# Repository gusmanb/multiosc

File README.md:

# MultiOsc
----
## Description
Two-channel 7Khz to 200Mhz clock/oscillator.

----
## Overview
MultiOsc is a very cheap two-channel clock generator which can be configured to generate frequencies from 8Khz to 200Mhz (180 to 200, depends on the SI5153 version) for less than 10€.

The device is based on the SI5351 clock generator, more concretely using the module sold in AliExpress (for less than 4€) which is very convenient as it already contains all the required external components to get it working immediately.

The device uses a STM32F103 module to control the clock generator and drive a 0.66" I2C screen.

## Schematic

The schematic is extremely simple, the three modules are connected through the I2C bus and five push buttons are used to control de menus, nothing more nothing else :)

## PCB

I also have included a very basic PCB to construct the device but it's not needed at all. I have assembled it using a protoboard and it works really well, but for anyone who wants to make it more robust the PCB is a good option.

Both, schematic and PCB are included under the "PCB" folder, it's a KiCad 6.0 project and it includes all the custom footprints for the modules in case you want to reuse them.

## BOM

The bill of materials is very reduced:

* STM32F103 module:  https://es.aliexpress.com/item/1005002441720435.html
* 0.66" OLED screen: https://es.aliexpress.com/item/1005002760899272.html
* SI5351 module:     https://es.aliexpress.com/item/32915414654.html
* Push buttons (5):  https://es.aliexpress.com/item/1005004001434474.html

I am 99.99999% sure the STM module uses a clone uC, not an original STM device, but as far as I can tell the device works flawlessly.

## STM32F103 bootloader

I have seen a lot of people complaining about the F103 modules failing to run the bootloader, but this is all a missunderstanding on how the bootloader works for the F103.

If you check carefully the [AN2606](https://www.st.com/resource/en/application_note/cd00167594-stm32-microcontroller-system-memory-boot-mode-stmicroelectronics.pdf) it clarifies the problem and is really simple, the STM32F10XXX family only has UART bootloader and the modules connect the USB connector to the USB pins from these devices, there is no integrated serial-to-usb converter so the bootloader will not work connecting only the USB port, you also need a serial-to-usb converter and connect it to pins PA9 and PA10, with this the device will be accessible from STM32CubeProgrammer.

In any case I recommend to use a ST-LINK/V2 or similar (I have an original one and a clone, both work but the original one is less prone to cause errors and can be upgraded, so if you can, buy an original one), it works a lot faster and allows to debug the code in real time.

## Firmware

The firmware project is a STM32CubeIde project, currently I have used the 1.9.0 version and it uses the standard drivers and two heavily modified libraries.

The first library is the SSD1306 library by afiskon and you can find the original here: https://github.com/afiskon/stm32-ssd1306
The second library is the SI5351 library by MR-DOS and you can find the original here: https://github.com/MR-DOS/Si5351-lib

As you can imagine the firmware itself is very simple, it creates a menu where you can change the two output frequencies and that's all, nothing else is needed, and as it relies on the two aforementioned libraries controlling the screen and the SI module is a breeze.

Beware that I found there is a problem with CubeMX, if you open the CubeMX file to reconfigure the HAL drivers, pinout or whatever the CubeMX does break the I2C configuration, for the F103 device it does not allow to configure the port speed and without the configuration the I2C bus does not work. If you need to reconfigure the hardware, after re-generating the files you will need to modify the file "stm32f1xx_hal_msp.c" and add to the I2C initialization, before the "HAL_GPIO_Init" call, this: 

	GPIO_InitStruct.Speed = GPIO_SPEED_FREQ_HIGH;

---

Have fun!

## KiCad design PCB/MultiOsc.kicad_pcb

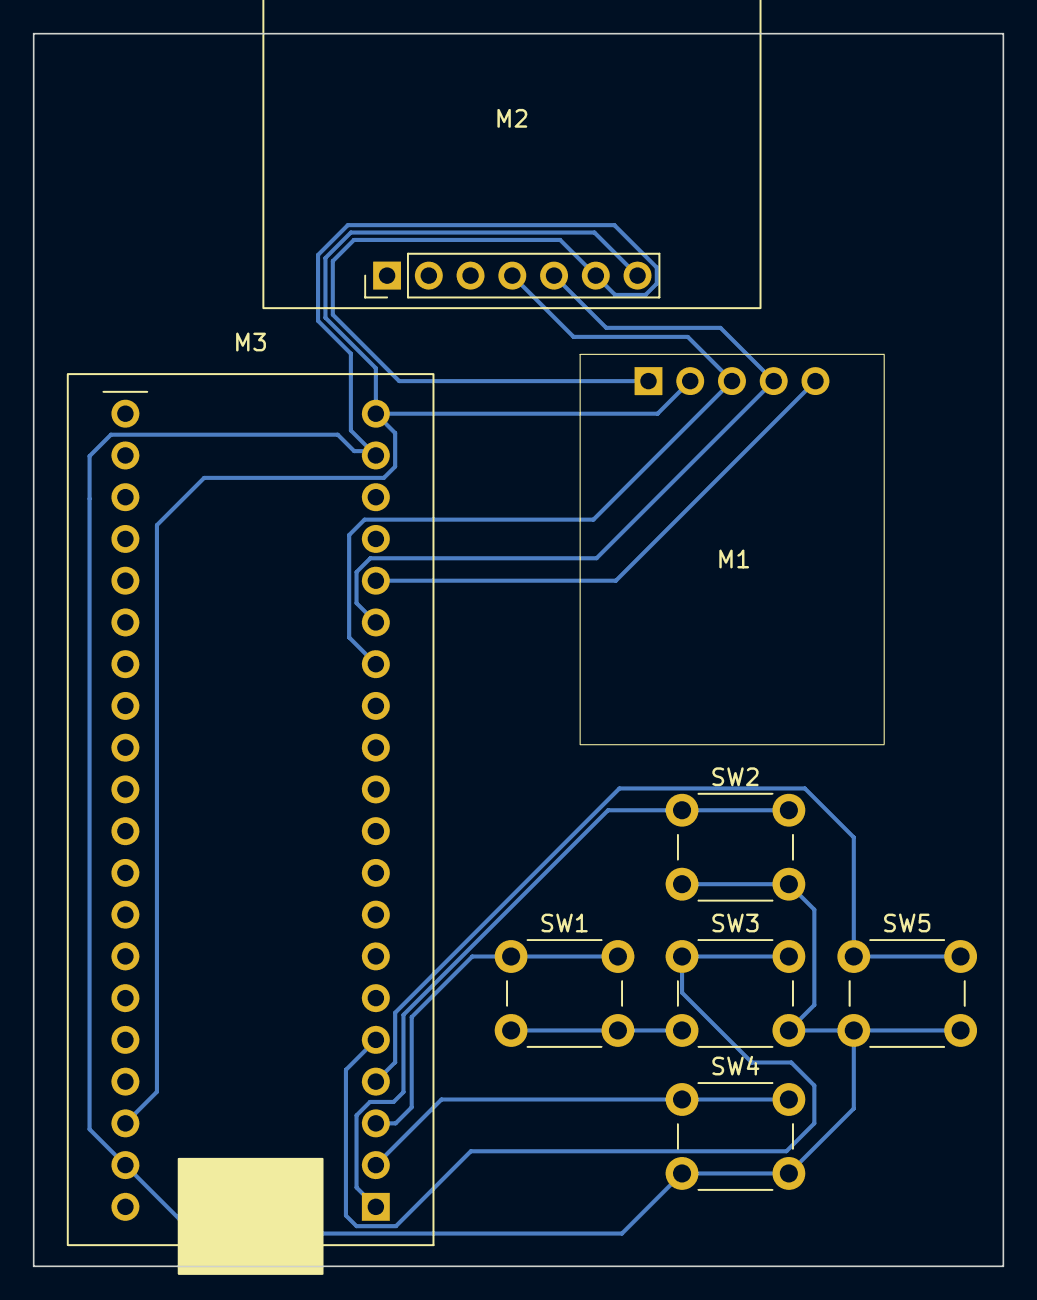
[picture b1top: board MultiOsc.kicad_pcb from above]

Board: 2 copper layers, 59.0 x 75.0 mm, 8 parts (0 on the bottom side), 10 nets.

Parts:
M1: OLED_066_Module
M2: SI5351_Module
M3: STM32F103_Module
SW1, SW2, SW3, SW4, SW5: SW_Push; SW_PUSH_6mm_H7.3mm

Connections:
/BTN_DOWN: M3.2 (B13), SW4.1
/BTN_ENTER: M3.5 (A8), SW3.1
/BTN_LEFT: M3.3 (B14), SW1.1
/BTN_RIGHT: M3.4 (B15), SW5.1
/BTN_UP: M3.1 (B12), SW2.1
/I2C_SCL: M1.3 (SCL), M2.4 (SCL), M3.14 (B6)
/I2C_SDA: M1.4 (SDA), M2.5 (SDA), M3.15 (B7)
/OLED_RES: M1.5 (RST), M3.16 (B8)
GND: M1.1 (GND), M2.6 (GND), M3.19 (G), M3.39 (G), SW1.2, SW2.2, SW3.2, SW4.2, SW5.2
VCC: M1.2 (VDD), M2.7 (VIN), M3.20 (3.3), M3.38 (3.3)

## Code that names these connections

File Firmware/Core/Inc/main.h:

/* USER CODE BEGIN Header */
/**
  ******************************************************************************
  * @file           : main.h
  * @brief          : Header for main.c file.
  *                   This file contains the common defines of the application.
  ******************************************************************************
  * @attention
  *
  * Copyright (c) 2022 STMicroelectronics.
  * All rights reserved.
  *
  * This software is licensed under terms that can be found in the LICENSE file
  * in the root directory of this software component.
  * If no LICENSE file comes with this software, it is provided AS-IS.
  *
  ******************************************************************************
  */
/* USER CODE END Header */

/* Define to prevent recursive inclusion -------------------------------------*/
#ifndef __MAIN_H
#define __MAIN_H

#ifdef __cplusplus
extern "C" {
#endif

/* Includes ------------------------------------------------------------------*/
#include "stm32f1xx_hal.h"

/* Private includes ----------------------------------------------------------*/
/* USER CODE BEGIN Includes */
#include "si5351.h"
#include "ssd1306.h"
/* USER CODE END Includes */

/* Exported types ------------------------------------------------------------*/
/* USER CODE BEGIN ET */

/* USER CODE END ET */

/* Exported constants --------------------------------------------------------*/
/* USER CODE BEGIN EC */

/* USER CODE END EC */

/* Exported macro ------------------------------------------------------------*/
/* USER CODE BEGIN EM */

/* USER CODE END EM */

/* Exported functions prototypes ---------------------------------------------*/
void Error_Handler(void);

/* USER CODE BEGIN EFP */

/* USER CODE END EFP */

/* Private defines -----------------------------------------------------------*/
#define LED_Pin GPIO_PIN_13
#define LED_GPIO_Port GPIOC
#define BTN_UP_Pin GPIO_PIN_12
#define BTN_UP_GPIO_Port GPIOB
#define BTN_DOWN_Pin GPIO_PIN_13
#define BTN_DOWN_GPIO_Port GPIOB
#define BTN_LEFT_Pin GPIO_PIN_14
#define BTN_LEFT_GPIO_Port GPIOB
#define BTN_RIGHT_Pin GPIO_PIN_15
#define BTN_RIGHT_GPIO_Port GPIOB
#define BTN_ENTER_Pin GPIO_PIN_8
#define BTN_ENTER_GPIO_Port GPIOA
#define OLED_RESET_PIN_Pin GPIO_PIN_8
#define OLED_RESET_PIN_GPIO_Port GPIOB
/* USER CODE BEGIN Private defines */

/* USER CODE END Private defines */

#ifdef __cplusplus
}
#endif

#endif /* __MAIN_H */
